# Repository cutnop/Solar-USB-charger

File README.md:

Solar-USB-charger
=================

Eagle files for a solar USB charger

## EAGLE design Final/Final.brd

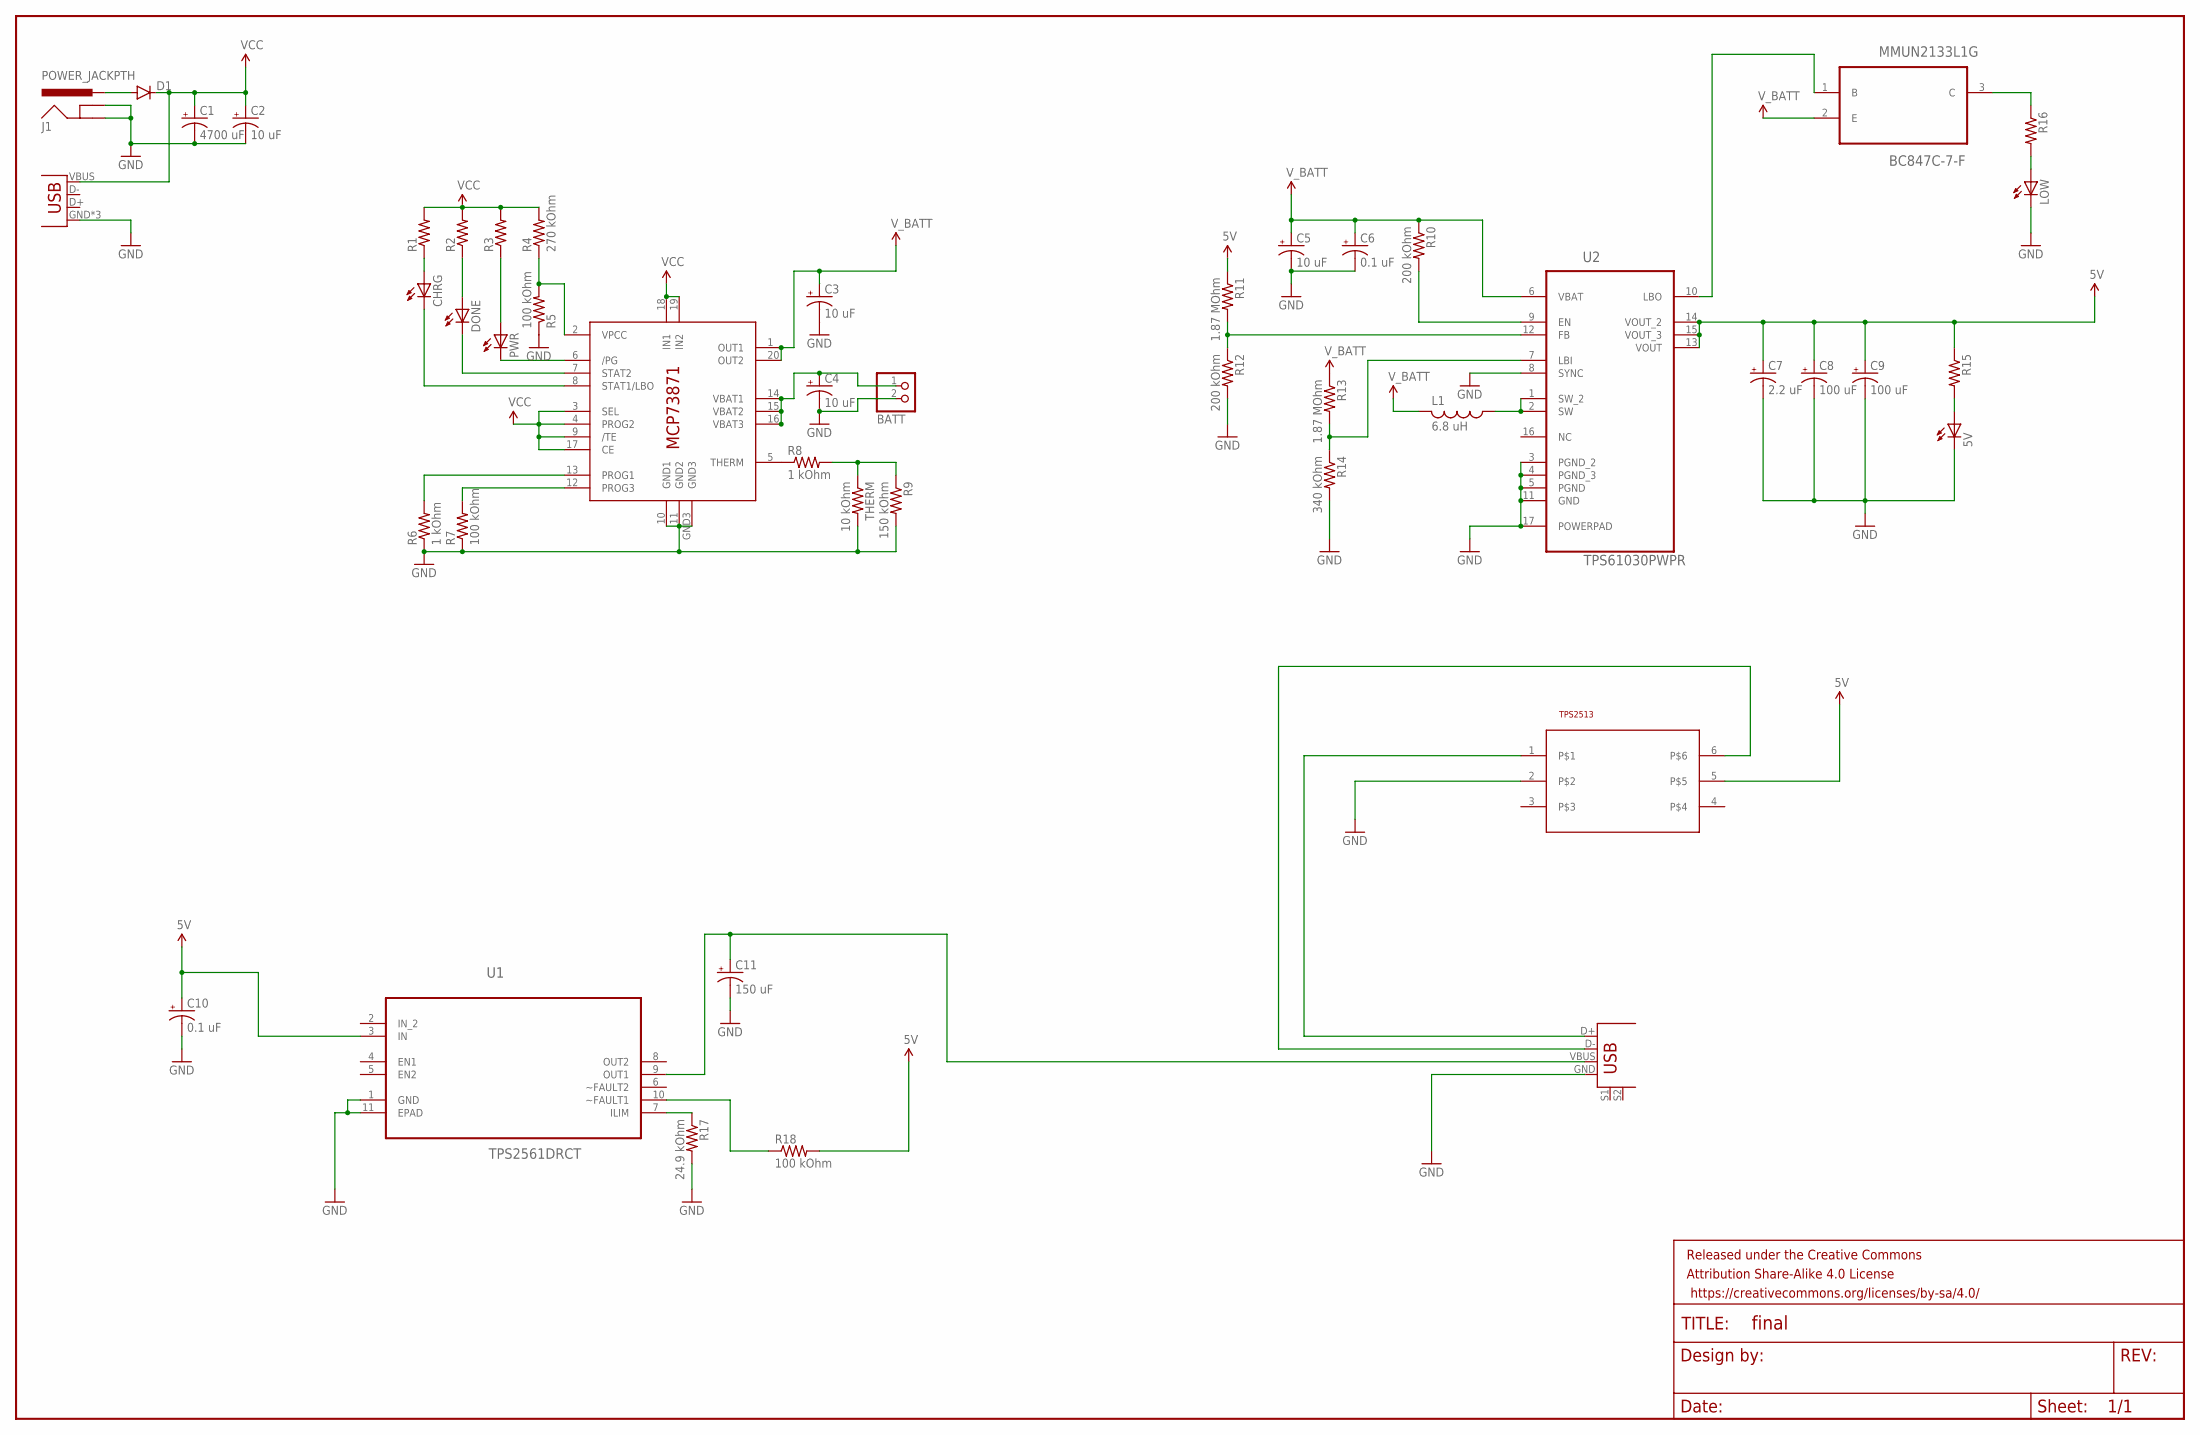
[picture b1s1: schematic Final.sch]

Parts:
5V: LED5MM
BATT: JST_2PIN-SMT-RA; JST-PH-2-SMT-RA
C1: 4700 uF; E7,5-16
C2, C3, C4, C5: 10 uF; E2,5-5
C6, C10: 0.1 uF; E2,5-5
C7: 2.2 uF; E2,5-5
C8, C9: 100 uF; E2,5-5
C11: 150 uF; E2,5-5
CHRG: LED5MM
D1: DIODEPTH; DIODE-1N4001
DONE: LED5MM
FRAME1: FRAME-LEDGER; CREATIVE_COMMONS
IC1: MCP73871; QFN20
J1: POWER_JACKPTH; POWER_JACK_PTH
L1: 6.8 uH; LAL03
LOW: LED5MM
MMUN2133L1G: BC847C-7-F; SOT103P240X110-3N
PWR: LED5MM
R1, R2, R3, R15, R16: R-US_0207/10; 0207/10
R4: 270 kOhm; 0207/10
R5, R7, R18: 100 kOhm; 0207/10
R6, R8: 1 kOhm; 0207/10
R9: 150 kOhm; 0207/10
R10, R12: 200 kOhm; 0207/10
R11, R13: 1.87 MOhm; 0207/10
R14: 340 kOhm; 0207/10
R17: 24.9 kOhm; 0207/10
THERM: 10 kOhm; 0207/10
TPS2513: TPS2513; SOT23-6
U1: TPS2561DRCT; SON50P300X300X100-11N
U2: TPS61030PWPR; SOP65P640X120-17N
U3: USB-MICROB
U$1: USB+SHIELDUSB-A-S-NOSILK-FEMALE; USB-A-S-NOSILK-FEMALE

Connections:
5V: C7.+, C8.+, C9.+, C10.+, R11.1, R15.1, R18.2, TPS2513.5, U1.3 (IN), U2.13 (VOUT), U2.14 (VOUT_2), U2.15 (VOUT_3)
GND: 5V.K (C), BATT.2 (1), C1.-, C2.-, C3.-, C4.-, C5.-, C6.-, C7.-, C8.-, C9.-, C10.-, C11.-, IC1.10 (GND1), IC1.11 (GND2), IC1.GND3, J1.GND, J1.GNDBREAK, LOW.K (C), R5.1, R6.1, R7.1, R9.2, R12.2, R14.2, R17.2, THERM.2, TPS2513.2, U1.1 (GND), U1.11 (EPAD), U2.3 (PGND_2), U2.4 (PGND_3), U2.5 (PGND), U2.8 (SYNC), U2.11 (GND), U2.17 (POWERPAD), U3.GND, U3.MT1 (GND), U3.MT2 (GND), U$1.GND
IN_2: U1.2 (IN_2)
unnamed: D1.A, J1.PWR
unnamed: IC1.2 (VPCC), R4.1, R5.2
unnamed: BATT.1 (2), C4.+, IC1.14 (VBAT1), IC1.15 (VBAT2), IC1.16 (VBAT3)
unnamed: IC1.12 (PROG3), R7.2
unnamed: CHRG.A, R1.1
unnamed: DONE.A, R2.1
unnamed: PWR.A, R3.1
unnamed: DONE.K (C), IC1.7 (STAT2)
unnamed: CHRG.K (C), IC1.8 (STAT1/LBO)
unnamed: IC1.13 (PROG1), R6.2
unnamed: IC1.5 (THERM), R8.1
unnamed: R8.2, R9.1, THERM.1
unnamed: IC1.6 (/PG), PWR.K (C)
unnamed: R13.2, R14.1, U2.7 (LBI)
unnamed: R11.2, R12.1, U2.12 (FB)
unnamed: 5V.A, R15.2
unnamed: L1.1, U2.1 (SW_2), U2.2 (SW)
unnamed: R10.2, U2.9 (EN)
unnamed: MMUN2133L1G.1 (B), U2.10 (LBO)
unnamed: R17.1, U1.7 (ILIM)
unnamed: MMUN2133L1G.3 (C), R16.1
unnamed: LOW.A, R16.2
unnamed: R18.1, U1.10 (~FAULT1)
unnamed: C11.+, U1.9 (OUT1), U$1.VBUS
unnamed: TPS2513.1, U$1.D+
unnamed: TPS2513.6, U$1.D-
VCC: C1.+, C2.+, D1.C, IC1.3 (SEL), IC1.4 (PROG2), IC1.9 (/TE), IC1.17 (CE), IC1.18 (IN1), IC1.19 (IN2), R1.2, R2.2, R3.2, R4.2, U3.VBUS
V_BATT: C3.+, C5.+, C6.+, IC1.1 (OUT1), IC1.20 (OUT2), L1.2, MMUN2133L1G.2 (E), R10.1, R13.1, U2.6 (VBAT)

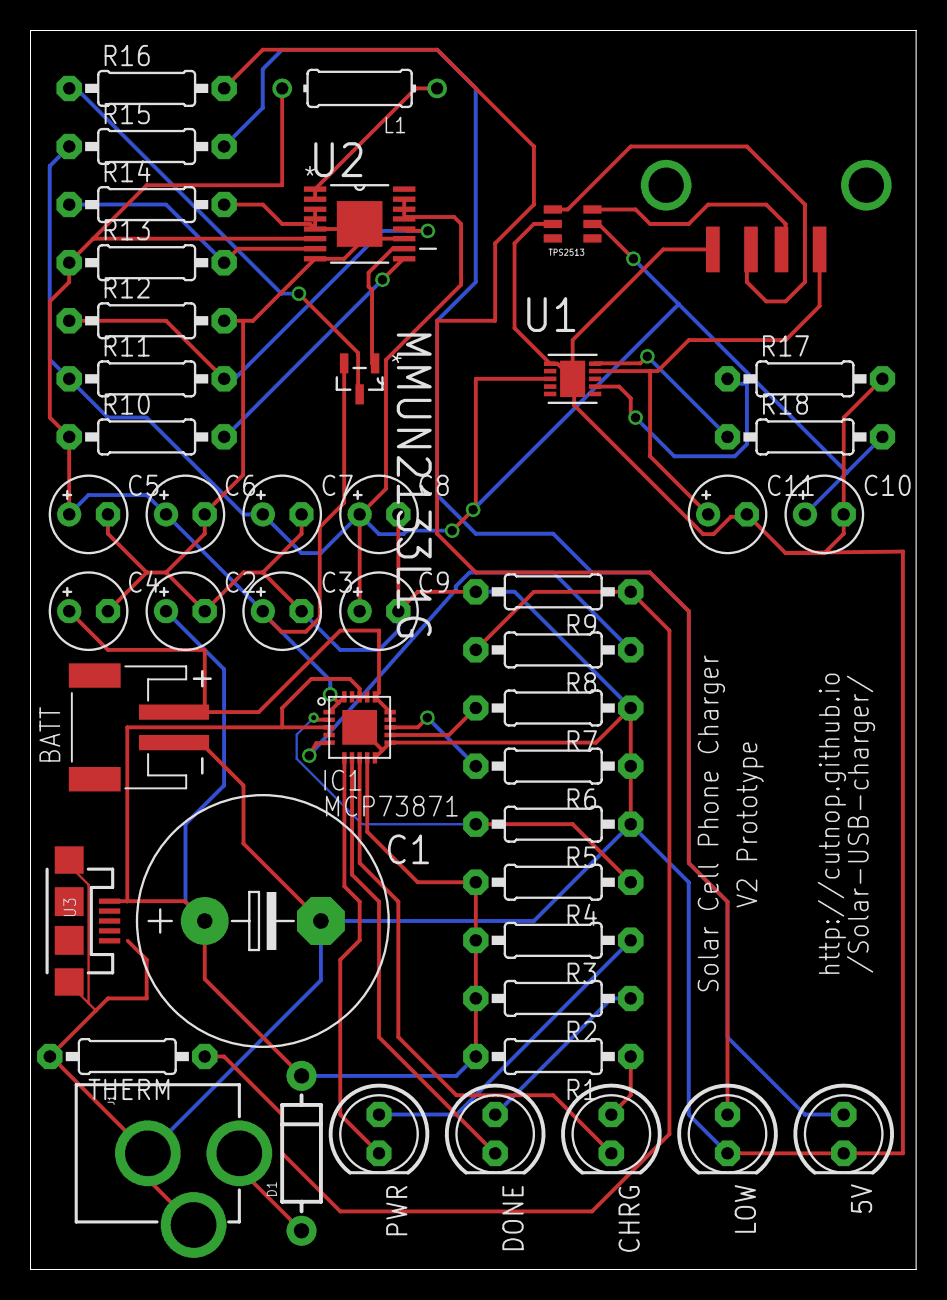
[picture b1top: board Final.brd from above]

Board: 2 copper layers, 58.1 x 81.3 mm, 47 parts (0 on the bottom side), 30 nets.

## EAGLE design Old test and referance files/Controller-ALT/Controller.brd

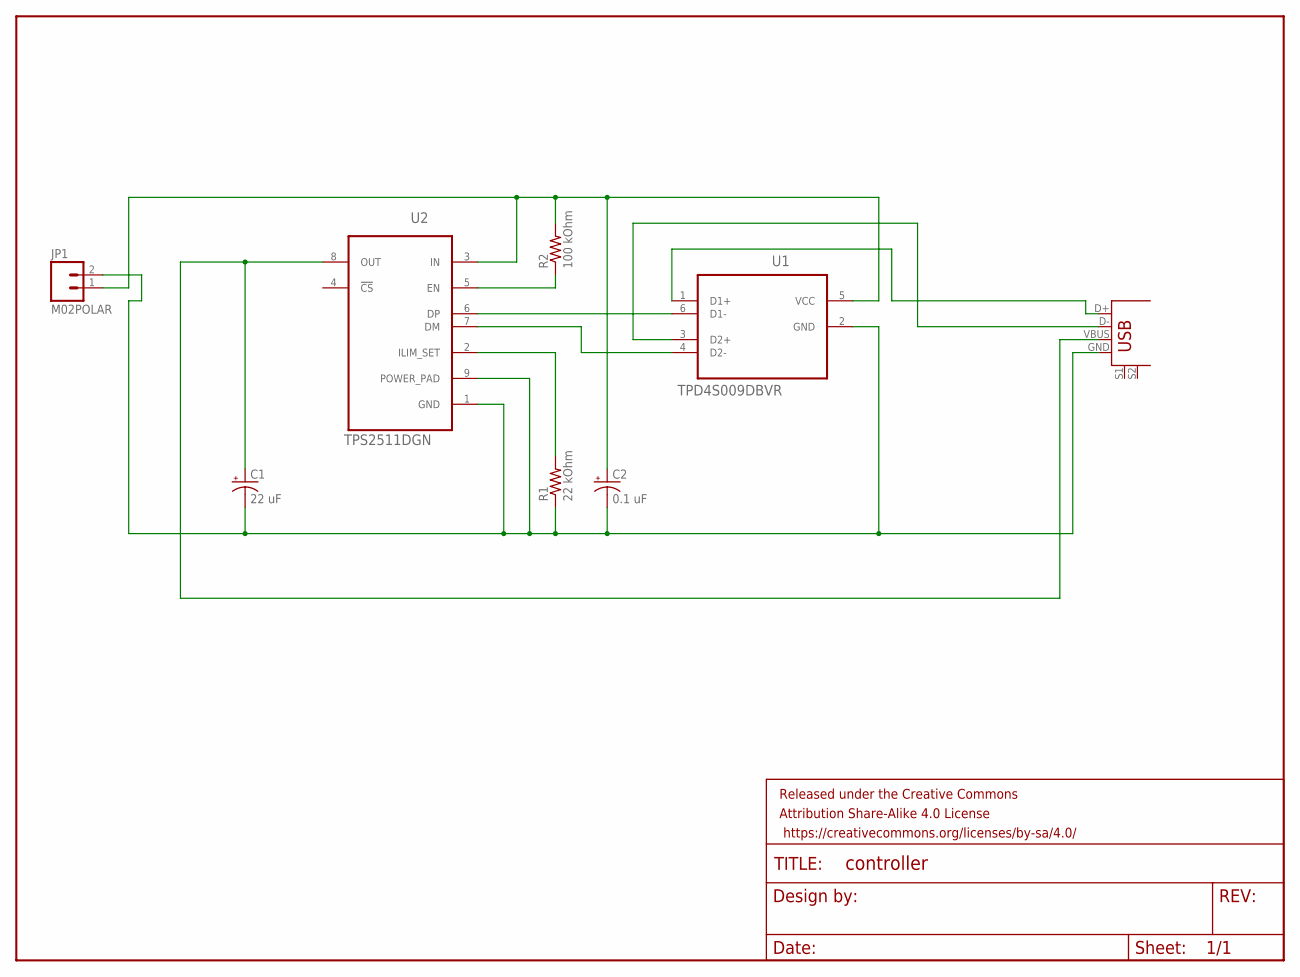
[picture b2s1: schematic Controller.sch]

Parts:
C1: 22 uF; E2,5-5
C2: 0.1 uF; E2,5-5
FRAME1: FRAME-LETTER; CREATIVE_COMMONS
JP1: M02POLAR; MOLEX-1X2
R1: 22 kOhm; 0207/10
R2: 100 kOhm; 0207/10
U1: TPD4S009DBVR; SOT95P280X145-6N
U2: TPS2511DGN; SOP65P490X110-9N
U$2: USB+SHIELDUSB-A-S-NOSILK-FEMALE; USB-A-S-NOSILK-FEMALE

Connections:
unnamed: R2.1, U2.5 (EN)
unnamed: C2.+, JP1.1, R2.2, U1.5 (VCC), U2.3 (IN)
unnamed: U1.6 (D1-), U2.6 (DP)
unnamed: U1.4 (D2-), U2.7 (DM)
unnamed: R1.2, U2.2 (ILIM_SET)
unnamed: C1.-, C2.-, JP1.2, R1.1, U1.2 (GND), U2.1 (GND), U2.9 (POWER_PAD), U$2.GND
unnamed: U1.1 (D1+), U$2.D+
unnamed: U1.3 (D2+), U$2.D-
unnamed: C1.+, U2.8 (OUT), U$2.VBUS

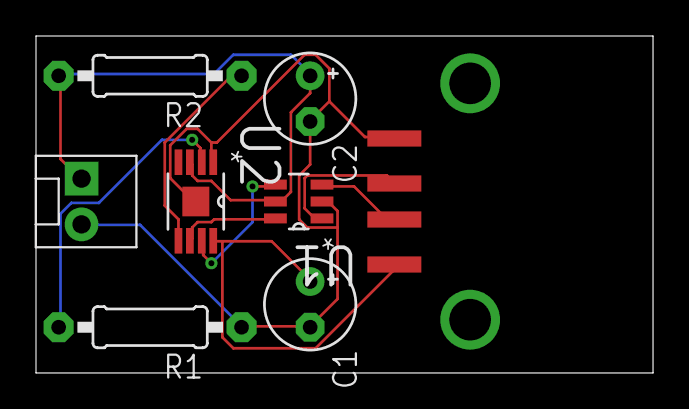
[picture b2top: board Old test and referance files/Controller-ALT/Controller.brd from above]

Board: 2 copper layers, 34.3 x 18.7 mm, 9 parts (0 on the bottom side), 9 nets.

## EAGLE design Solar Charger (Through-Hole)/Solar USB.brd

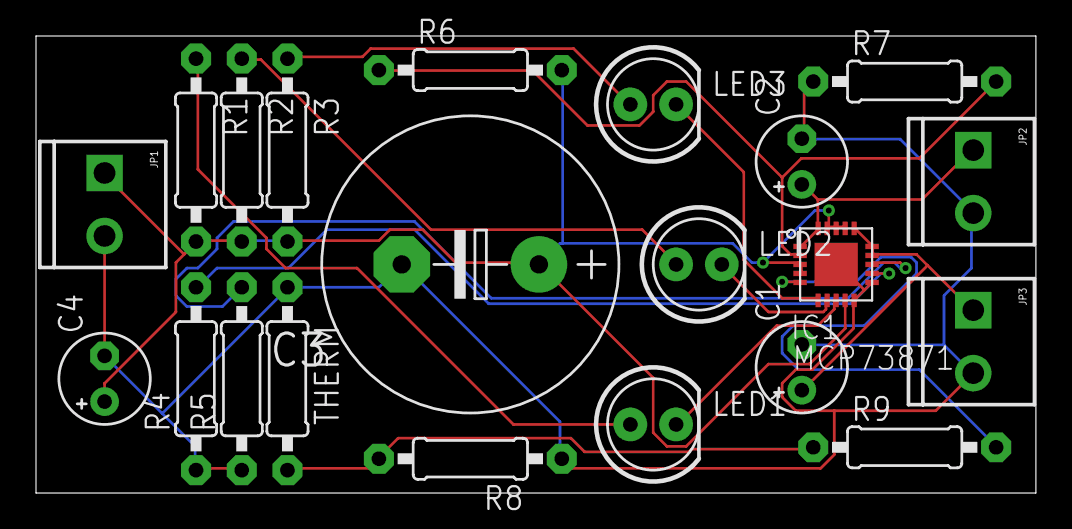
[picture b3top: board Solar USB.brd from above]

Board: 2 copper layers, 55.5 x 25.4 mm, 22 parts (0 on the bottom side), 15 nets.

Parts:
C1, C2, C4: 10uF; E2,5-5
C3: 4700uF; E7,5-16
FRAME1: FRAME-LETTER; CREATIVE_COMMONS
IC1: MCP73871; QFN20
JP1, JP2, JP3: M023.5MM; SCREWTERMINAL-3.5MM-2
LED1, LED2, LED3: LED5MM
R1, R2, R3: 0207/10
R4, R7: 100k; 0207/10
R5, R9: 1k; 0207/10
R6: 270k; 0207/10
R8: 150k; 0207/10
THERM: 10k; 0207/10

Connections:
unnamed: IC1.6, LED3.K
unnamed: C1.-, C2.-, C3.-, C4.-, IC1.10, IC1.11, IC1.21, JP1.2, JP2.2, JP3.2, R4.1, R5.1, R7.1, R8.1, THERM.1
unnamed: IC1.12, R4.2
unnamed: IC1.13, R5.2
unnamed: R8.2, R9.1, THERM.2
unnamed: IC1.7, LED2.K
unnamed: IC1.8, LED1.K
unnamed: C3.+, C4.+, IC1.3, IC1.4, IC1.9, IC1.17, IC1.18, IC1.19, JP1.1, R1.2, R2.2, R3.2, R6.2
unnamed: IC1.5, R9.2
unnamed: LED1.A, R1.1
unnamed: LED2.A, R2.1
unnamed: LED3.A, R3.1
unnamed: C2.+, IC1.1, IC1.20, JP2.1
unnamed: IC1.2, R6.1, R7.2
unnamed: C1.+, IC1.14, IC1.15, IC1.16, JP3.1

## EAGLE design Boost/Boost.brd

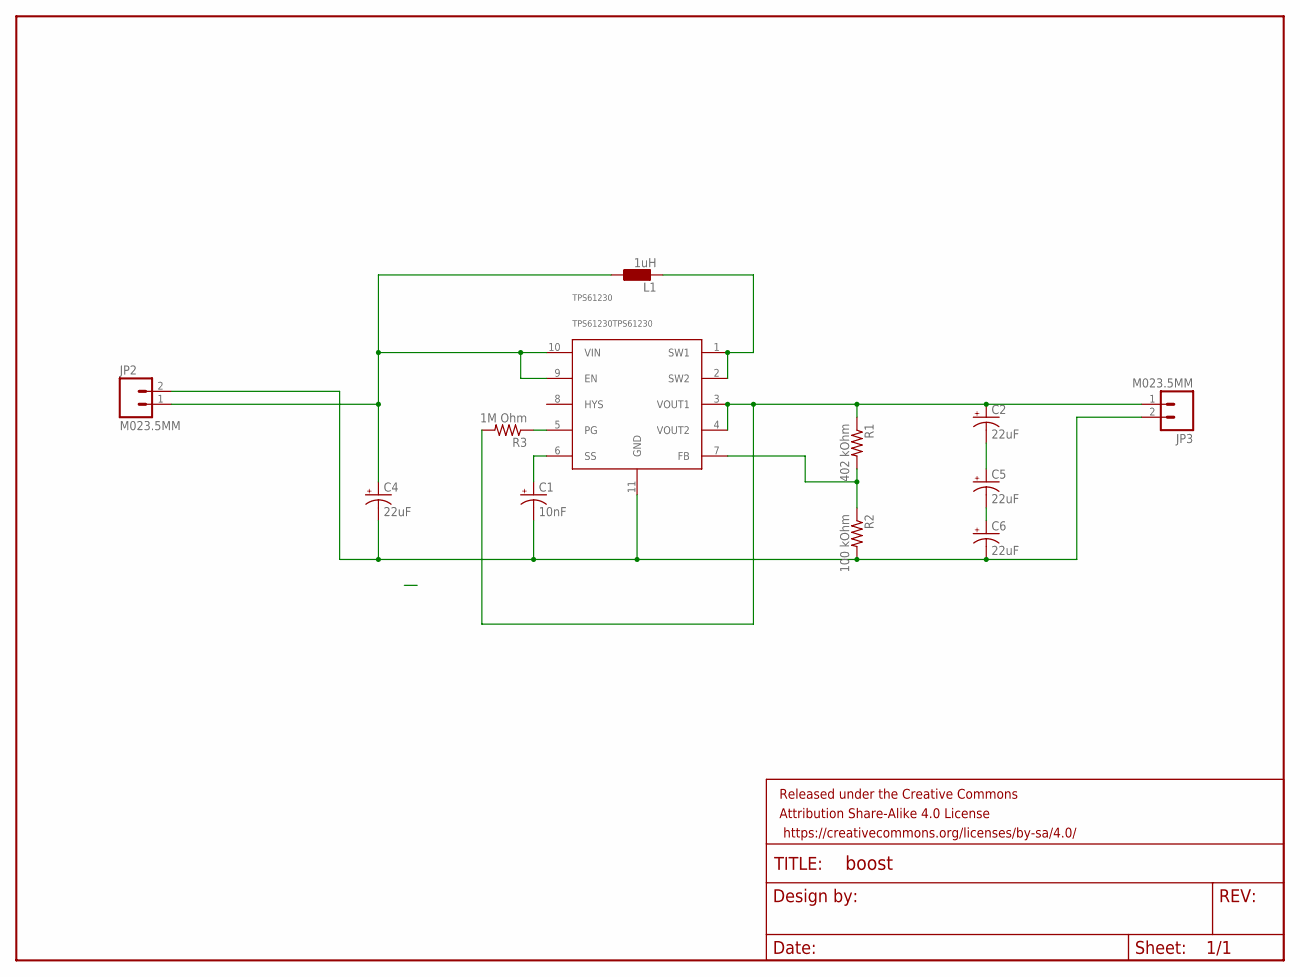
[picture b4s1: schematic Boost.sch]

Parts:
C1: 10nF; E2,5-5
C2, C4, C5, C6: 22uF; E2,5-5
FRAME1: FRAME-LETTER; CREATIVE_COMMONS
JP2, JP3: M023.5MM; SCREWTERMINAL-3.5MM-2
L1: 1uH; 0207/10
R1: 402 kOhm; 0207/10
R2: 100 kOhm; 0207/10
R3: 1M Ohm; 0207/10
TPS61230: TPS61230TPS61230; SON50P300X300X100-11N

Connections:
unnamed: C1.-, C4.-, C6.-, JP2.2, JP3.2, R2.2, TPS61230.11 (GND)
unnamed: R3.1, TPS61230.5 (PG)
unnamed: L1.2, TPS61230.1 (SW1), TPS61230.2 (SW2)
unnamed: C2.+, JP3.1, R1.1, R3.2, TPS61230.3 (VOUT1), TPS61230.4 (VOUT2)
unnamed: C1.+, TPS61230.6 (SS)
unnamed: C4.+, JP2.1, L1.1, TPS61230.9 (EN), TPS61230.10 (VIN)
unnamed: C5.-, C6.+
unnamed: C2.-, C5.+
unnamed: R1.2, R2.1, TPS61230.7 (FB)

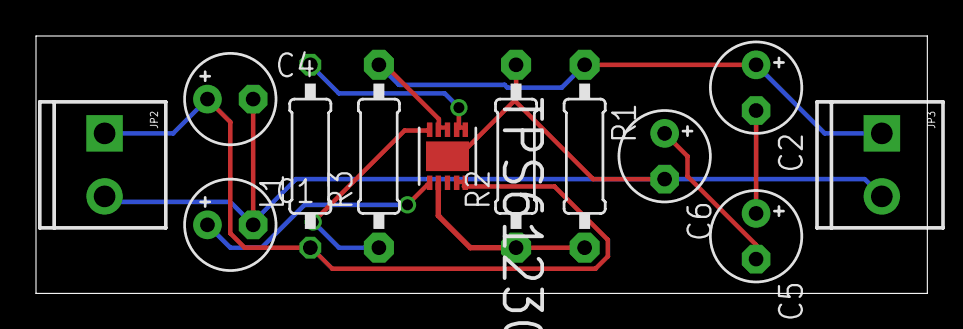
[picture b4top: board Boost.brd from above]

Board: 2 copper layers, 49.5 x 14.3 mm, 13 parts (0 on the bottom side), 9 nets.

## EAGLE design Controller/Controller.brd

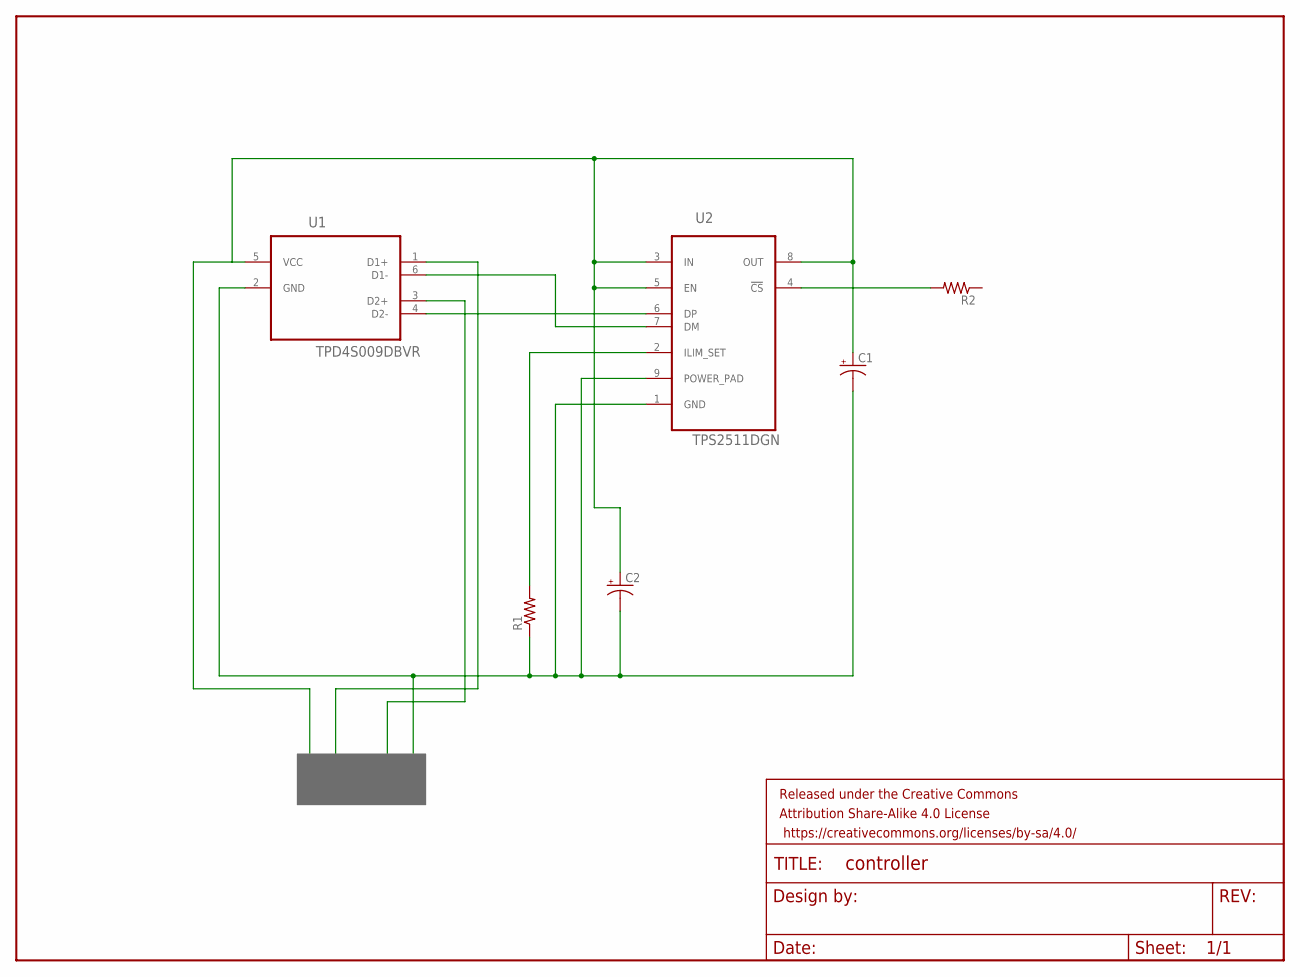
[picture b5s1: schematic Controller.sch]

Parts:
C1, C2: CPOL-USE2-5; E2-5
FRAME1: FRAME-LETTER; CREATIVE_COMMONS
R1, R2: RESISTORKIT; AXIAL-0.3-KIT
U1: TPD4S009DBVR; SOT95P280X145-6N
U2: TPS2511DGN; SOP65P490X110-9N

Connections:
unnamed: C1.+, C2.+, U1.5 (VCC), U2.3 (IN), U2.5 (EN), U2.8 (OUT)
unnamed: C1.-, C2.-, R1.P$1 (1), U1.2 (GND), U2.1 (GND), U2.9 (POWER_PAD)
unnamed: U1.6 (D1-), U2.7 (DM)
unnamed: U1.4 (D2-), U2.6 (DP)
unnamed: R1.P$2 (2), U2.2 (ILIM_SET)
unnamed: R2.P$2 (2), U2.4 (!CS)

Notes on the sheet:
GND
VCC
DATA+
DATA-

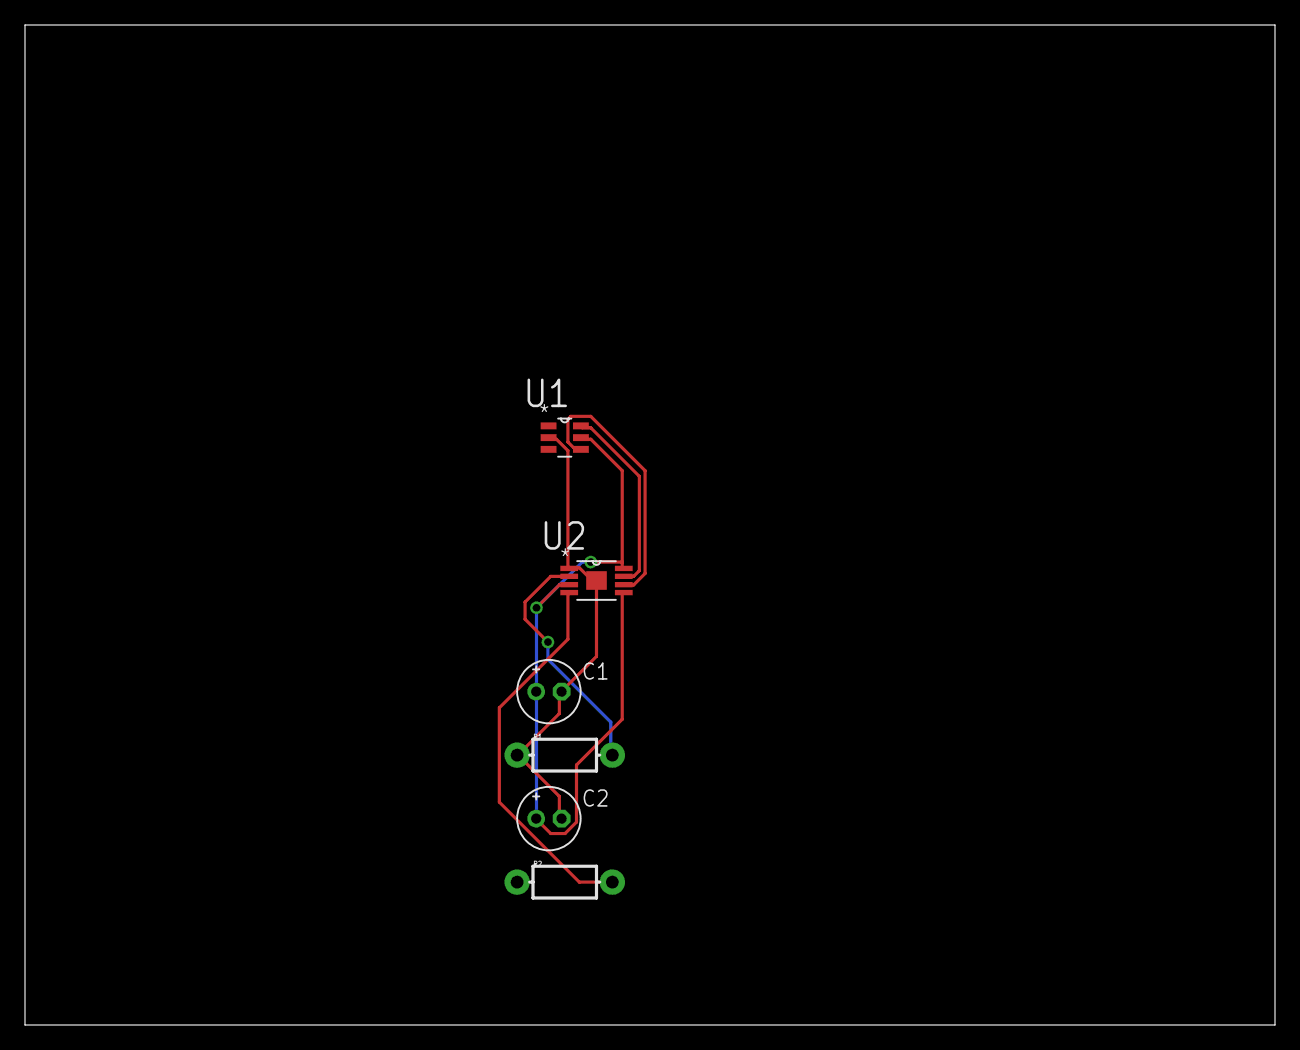
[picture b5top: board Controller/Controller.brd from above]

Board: 2 copper layers, 100.0 x 80.0 mm, 7 parts (0 on the bottom side), 6 nets.

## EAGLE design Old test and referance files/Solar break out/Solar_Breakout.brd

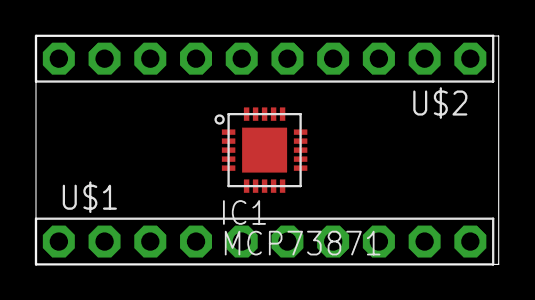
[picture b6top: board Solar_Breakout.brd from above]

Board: 2 copper layers, 25.7 x 12.7 mm, 3 parts (0 on the bottom side), 20 nets, no tracks yet.

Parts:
IC1: MCP73871; QFN20
U$1, U$2: PINHD-1X10; 1X10-BIG

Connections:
unnamed: IC1.1, U$1.1
unnamed: IC1.2, U$1.2
unnamed: IC1.3, U$1.3
unnamed: IC1.4, U$1.4
unnamed: IC1.5, U$1.5
unnamed: IC1.6, U$1.6
unnamed: IC1.7, U$1.7
unnamed: IC1.8, U$1.8
unnamed: IC1.9, U$1.9
unnamed: IC1.10, U$1.10
unnamed: IC1.11, U$2.1
unnamed: IC1.12, U$2.2
unnamed: IC1.13, U$2.3
unnamed: IC1.14, U$2.4
unnamed: IC1.15, U$2.5
unnamed: IC1.16, U$2.6
unnamed: IC1.17, U$2.7
unnamed: IC1.18, U$2.8
unnamed: IC1.19, U$2.9
unnamed: IC1.20, U$2.10

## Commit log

2014-10-16 Added Solar Through-Hole .brd and .sch
2014-10-16 Create gh-pages branch via GitHub
2014-10-16 Renamed previous file name and added Eagle lib.s
2014-10-16 Added controller folder and files.
2014-10-16 Added board.
2014-10-17 Modified controller.
2014-10-17 Added files.
2014-10-17 Created Boost Part and Start of Boost Project
2014-10-17 Added more libs
2014-10-17 Modified ESD/Controller board and schematic.
2014-10-17 No idea
2014-10-21 Modified controller
2014-10-21 boost
2014-10-22 Made some changes to feedback loop and reorganized controller
2014-10-22 No idea pt. 2
2014-11-18 Final started
    Added parts
2014-11-18 forgot
2014-11-18 added power parts
2014-11-18 moved stuff
2014-11-19 solar final done
2014-11-20 wired final solar
2014-11-20 wired up solar board
2014-11-21 wired boost sch and brd
2014-11-21 DONE!!!!
2014-11-24 Finished final design and reorganized folders
2014-11-24 Made even more tweeks to the design
2014-11-25 more tweeks

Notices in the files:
parts and their libraries:
SparkFun-Aesthetics: Licensing: Creative Commons ShareAlike 4.0 International - https://creativecommons.org/licenses/by-sa/4.0
SparkFun-Aesthetics: Released under the Creative Commons Attribution Share-Alike 4.0 License
SparkFun-Aesthetics: https://creativecommons.org/licenses/by-sa/4.0
